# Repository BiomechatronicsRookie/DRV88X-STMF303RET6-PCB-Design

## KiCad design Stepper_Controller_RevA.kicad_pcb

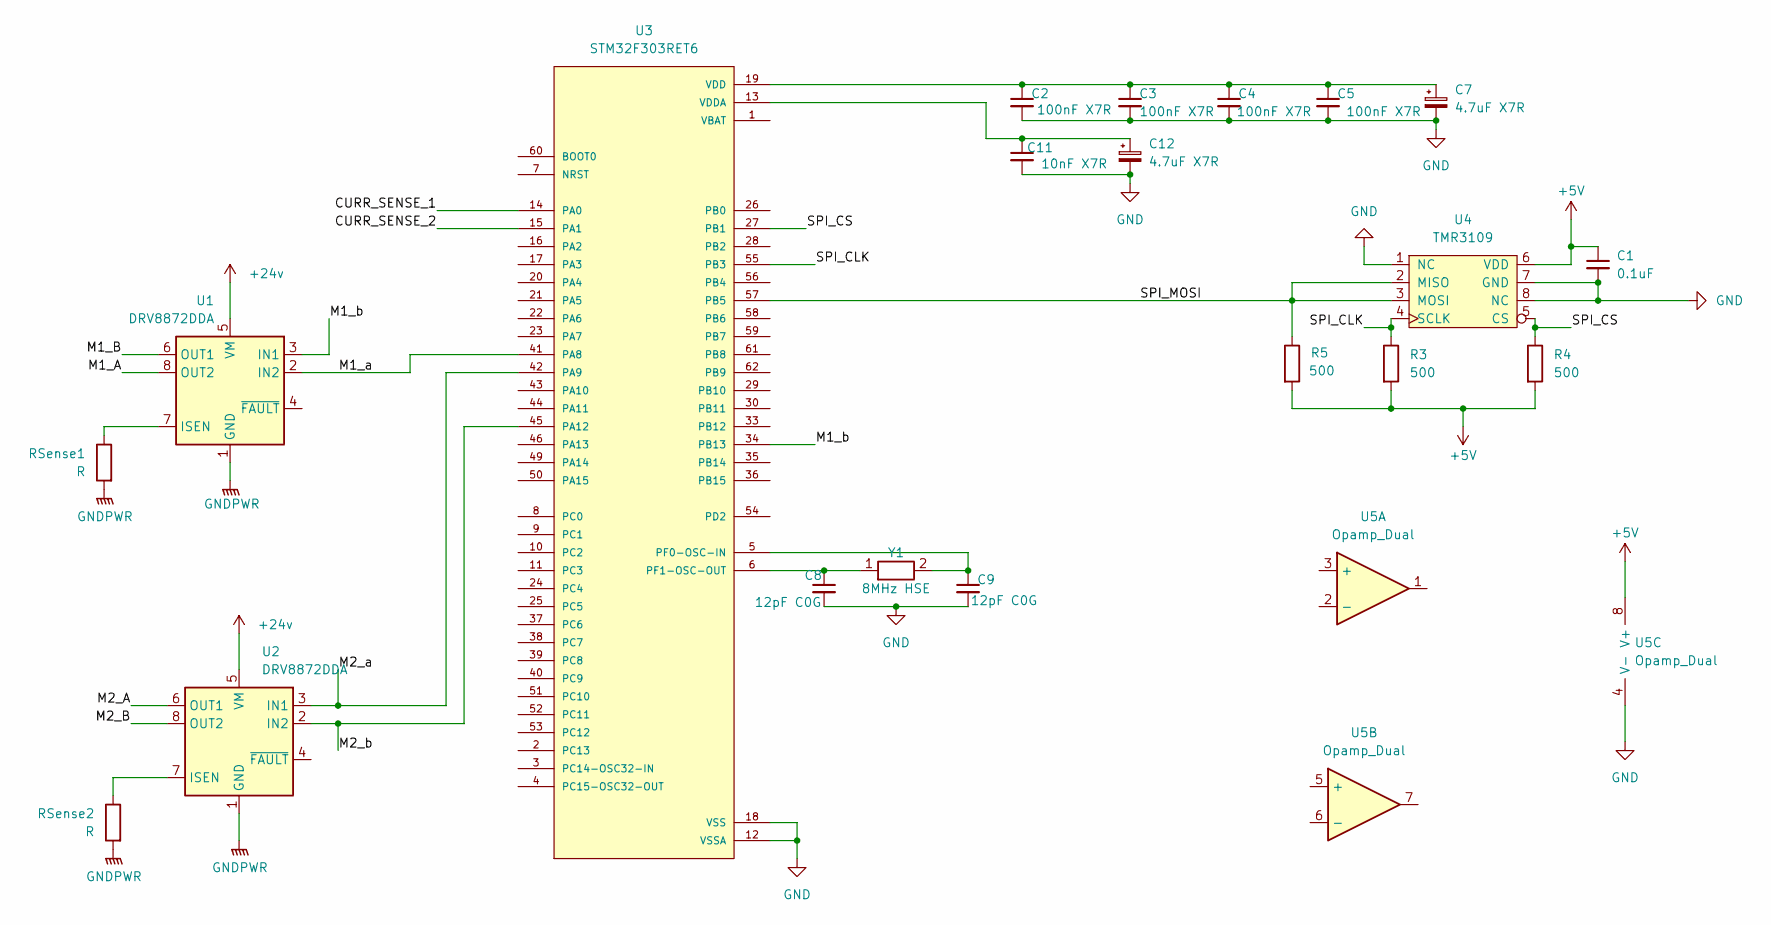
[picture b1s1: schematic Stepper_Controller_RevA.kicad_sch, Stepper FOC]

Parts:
C1: 0.1uF; C_0603_1608Metric
C2, C3, C4, C5: 100nF X7R; C_0603_1608Metric
C7, C12: 4.7uF X7R; C_0603_1608Metric
C8, C9: 12pF C0G; C_0603_1608Metric
C11: 10nF X7R; C_0603_1608Metric
R3, R4, R5: 500; R_0603_1608Metric_Pad0.98x0.95mm_HandSolder
RSense1, RSense2: R; R_0603_1608Metric_Pad0.98x0.95mm_HandSolder
U1, U2: DRV8872DDA; Texas_HTSOP-8-1EP_3.9x4.9mm_P1.27mm_EP2.95x4.9mm_Mask2.4x3.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
U3: STM32F303RET6; QFP50P1200X1200X160-64N; PARTREV 5
U4: TMR3109; TMR3109_SOIC-8_3.9x4.9mm_P1.27mm; MPN TMR3109P
U5: Opamp_Dual; SOIC-8_3.9x4.9mm_P1.27mm
Y1: 8MHz HSE; Crystal_SMD_3225-4Pin_3.2x2.5mm

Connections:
+5V: C1.1, R3.2, R4.2, R5.2, U4.6 (VDD), U5.8 (V+)
+24v: U1.5 (VM), U2.5 (VM)
/CURR_SENSE_1: U3.14 (PA0)
/CURR_SENSE_2: U3.15 (PA1)
/M1_A: U1.8 (OUT2)
/M1_B: U1.6 (OUT1)
/M1_a: U1.2 (IN2), U3.41 (PA8)
/M1_b: U1.3 (IN1), U3.34 (PB13)
/M2_A: U2.6 (OUT1)
/M2_B: U2.8 (OUT2)
/M2_a: U2.3 (IN1), U3.42 (PA9)
/M2_b: U2.2 (IN2), U3.45 (PA12)
/SPI_CLK: R3.1, U3.55 (PB3), U4.4 (SCLK)
/SPI_CS: R4.1, U3.27 (PB1), U4.5 (CS)
/SPI_MOSI: R5.1, U3.57 (PB5), U4.2 (MISO), U4.3 (MOSI)
GND: C1.2, C2.2, C3.2, C4.2, C5.2, C7.2, C8.2, C9.2, C11.2, C12.2, U3.12 (VSSA), U3.18 (VSS), U3.31 (VSS), U3.47 (VSS), U3.63 (VSS), U4.1 (NC), U4.7 (GND), U4.8 (NC), U5.4 (V-)
GNDPWR: RSense1.2, RSense2.2, U1.1 (GND), U1.9 (GND), U2.1 (GND), U2.9 (GND)
unnamed: RSense1.1, U1.7 (ISEN)
unnamed: RSense2.1, U2.7 (ISEN)
unnamed: C9.1, U3.5 (PF0-OSC-IN), Y1.2
unnamed: C8.1, U3.6 (PF1-OSC-OUT), Y1.1
unnamed: C11.1, C12.1, U3.13 (VDDA)
VDD: C2.1, C3.1, C4.1, C5.1, C7.1, U3.19 (VDD), U3.32 (VDD), U3.48 (VDD), U3.64 (VDD)

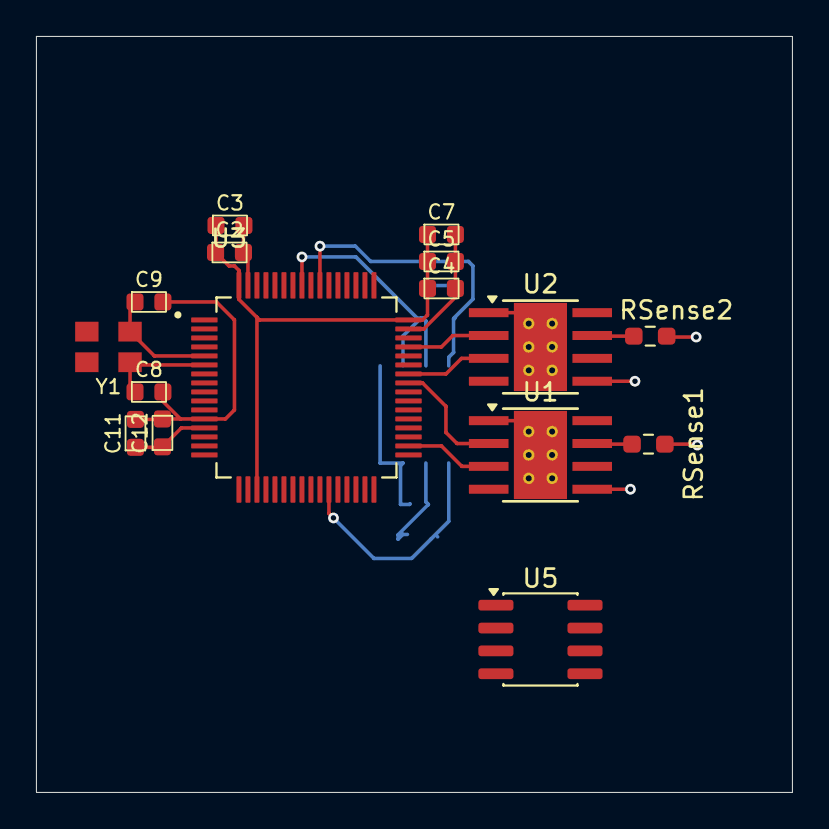
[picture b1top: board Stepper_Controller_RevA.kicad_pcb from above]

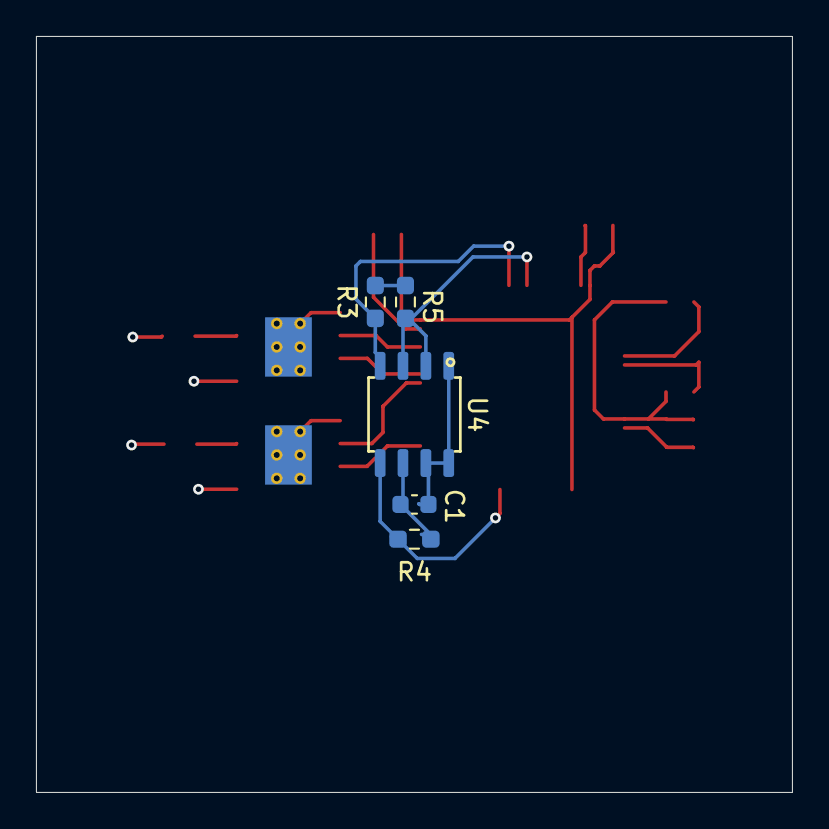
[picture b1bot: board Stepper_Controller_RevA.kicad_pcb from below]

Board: 4 copper layers, 42.0 x 42.0 mm, 21 parts (5 on the bottom side), 17 nets.
